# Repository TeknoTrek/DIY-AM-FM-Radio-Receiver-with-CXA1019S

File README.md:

# DIY AM/FM Radio Receiver with Sony CXA1019S - KiCad Project  

🚀 **Build your own high-quality AM/FM radio receiver** using the **Sony CXA1019S IC**! This repository contains the complete **KiCad PCB design**, schematic, and BOM for a powerful DIY radio project.  

🎥 **Watch the Full Build Tutorial on YouTube:**  
[👉 Click here to watch the video](https://youtu.be/TuUUNz7IGRk)

## 📌 Features  
✔ **Dual-band reception** (AM + FM)  
✔ **Low-noise Sony CXA1019S IC** for clear audio  
✔ **KiCad 6/7 compatible** design files  
✔ **Step-by-step YouTube tutorial** ([Watch Here](https://youtu.be/TuUUNz7IGRk))  

## 📁 Files Included
- 📐 Circuit schematic file (KiCad)
- 🧩 PCB layout
- 📸 Images and renders of the circuit
- 📄 Bill of materials (components list)

## 📦 Requirements
To complete this project, you’ll need:
- CXA1019S IC
- Basic electronic components (resistors, capacitors, etc.)
- Soldering iron & tools
- Access to KiCad (Free PCB design software)

## 🔧 How to Use  
1. **Download KiCad** (if you don’t have it): [kicad.org](https://www.kicad.org)  
2. Clone this repo or download the `.zip` file.  
3. Open the `.kicad_pro` file in KiCad to modify the design.  
4. Check the **BOM** for required components.  
5. Watch the **[assembly tutorial on YouTube](https://youtu.be/TuUUNz7IGRk)** for step-by-step guidance.  

## 📺 Watch the Full Tutorial  
  
Learn how to assemble and troubleshoot the circuit in the **[full video guide](https://youtu.be/TuUUNz7IGRk)** on the **TeknoTrek** channel!  

## 📸 Project Images

## 💬 Questions or Feedback?
Feel free to open an issue or leave a comment on the [YouTube video](https://youtu.be/TuUUNz7IGRk). I’d love to hear your thoughts and help if you get stuck!

## 📡 Tags & Keywords (for SEO)
`AM radio receiver`, `FM radio project`, `Sony CXA1019S`, `build a radio`, `DIY electronics`, `PCB design`, `KiCad project`, `radio circuit`, `home radio`, `electronics tutorial`, `radio IC`, `radio PCB`, `TeknoTrek`, `radio receiver project`, `electronics for beginners`

## ❓ FAQ  
**Q: Can I modify the PCB for better performance?**  
A: Yes! The KiCad files are fully editable. Optimize traces or add filters as needed.  

**Q: Where can I buy the CXA1019S IC?**  
A: Check AliExpress, eBay, or local electronics stores.  

## 🌟 Support the Project  
- **Give a ⭐ on GitHub** if you find this useful!  
- **Subscribe to [TeknoTrek on YouTube](https://www.youtube.com/@TeknoTrek)** for more DIY electronics projects.  
- **Share your build** in the Discussions section!  

📢 **Disclaimer**: This is an open-source project. Use at your own risk.  

#electronics #diy #radio #cxA1019s #pcbdesign #kicad #amfmradio #engineering #teknopatik

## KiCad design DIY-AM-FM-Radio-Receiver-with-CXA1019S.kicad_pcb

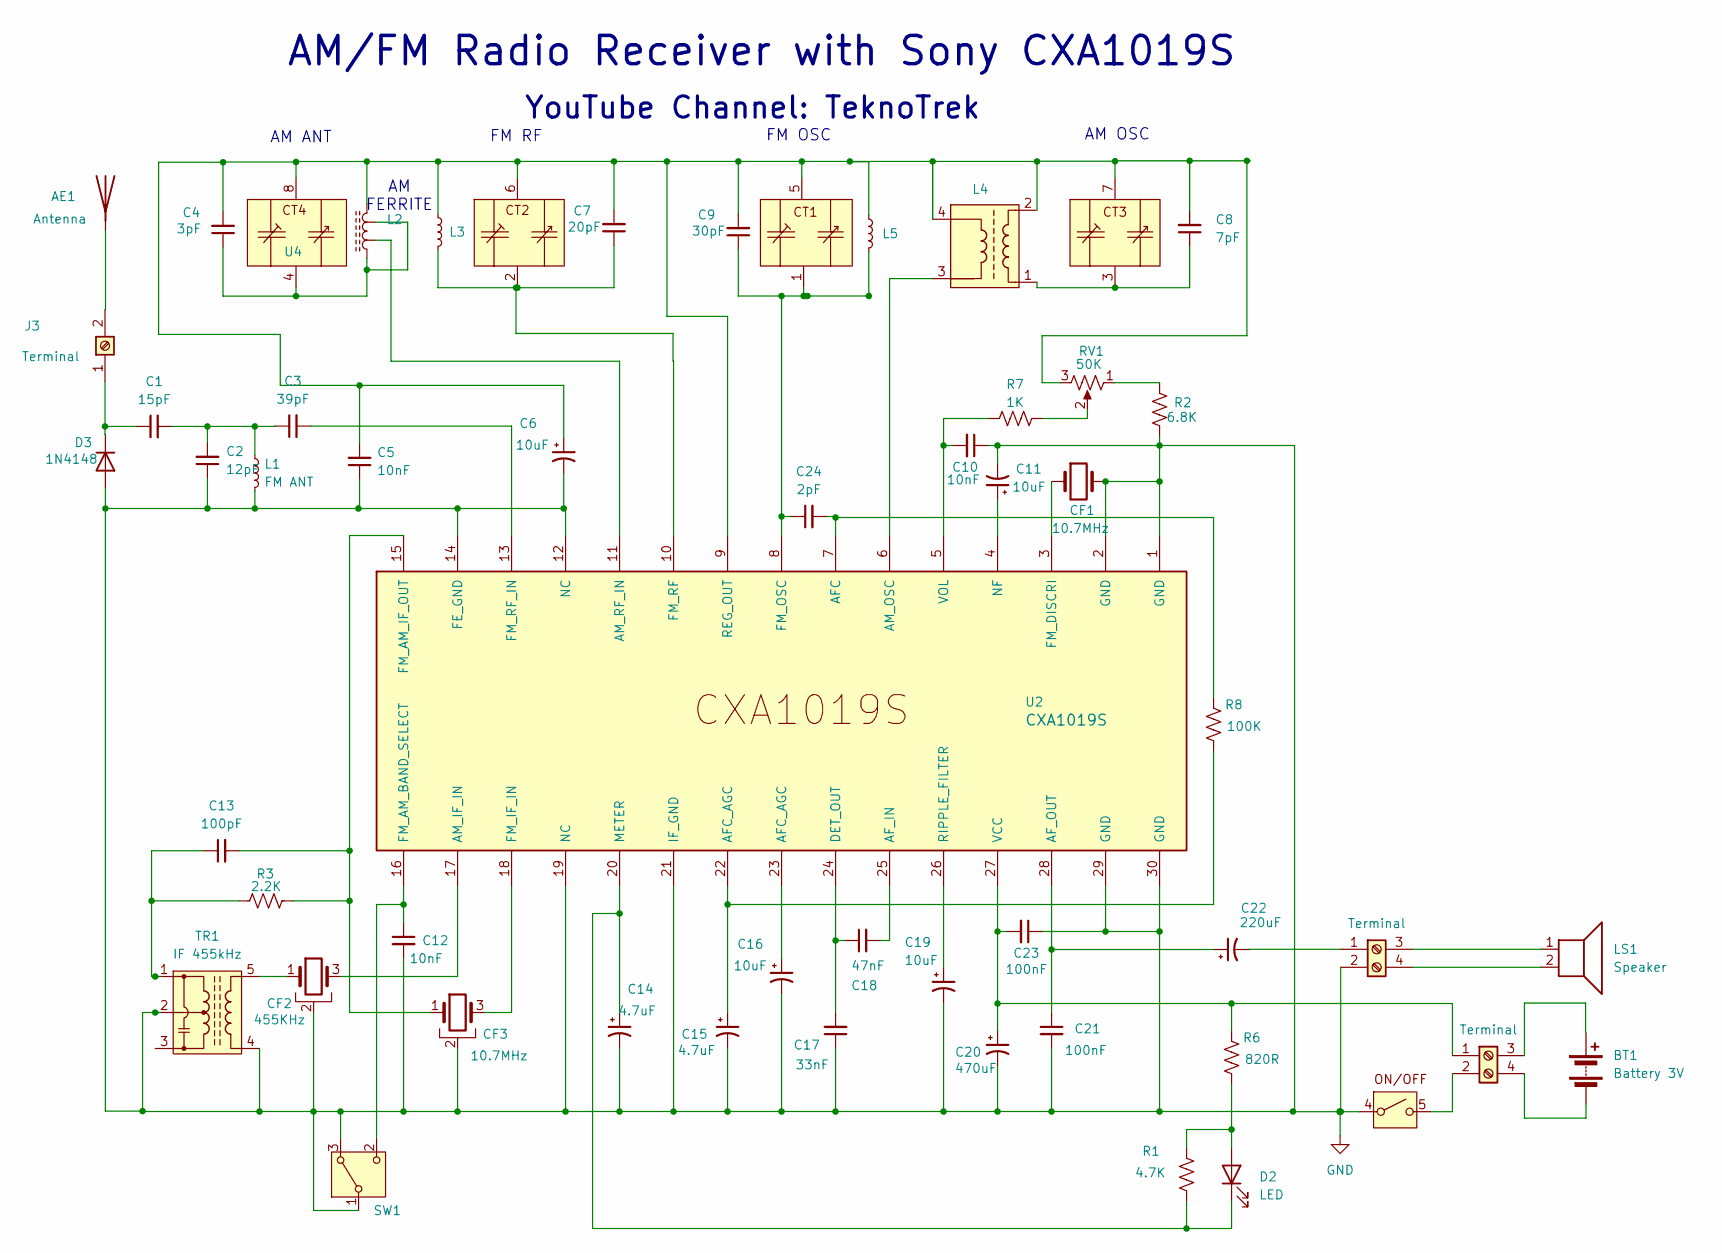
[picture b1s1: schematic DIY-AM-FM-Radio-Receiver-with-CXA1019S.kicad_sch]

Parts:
AE1: Antenna
BT1: Battery 3V
C1: 15pF; Standart_pF_Capasitor
C2: 12pF; Standart_pF_Capasitor
C3: 39pF; 39pF_Capasitor
C4: 3pF; Standart_pF_Capasitor
C5, C10, C12: 10nF; 10nF_Capasitor
C6, C11, C16, C19: 10uF; 10uF_Capasitor
C7: 20pF; Standart_pF_Capasitor
C8: 7pF; Standart_pF_Capasitor
C9: 30pF; Standart_pF_Capasitor
C13: 100pF; Standart_pF_Capasitor
C14, C15: 4.7uF; 4_7uF_Capasitor
C17: 33nF; 33nF_Capasitor
C18: 47nF; 47nF_Capasitor
C20: 470uF; 470uF_Capasitor
C21, C23: 100nF; 100nF_Capasitor
C22: 220uF; 220uF_Capasitor
C24: 2pF; 2_2pF_Capasitor
CF1: 10.7MHz; Resonator-2Pin_W6.0mm_H3.0mm
CF2: 455KHz; Resonator-3Pin_W7.0mm_H2.5mm
CF3: 10.7MHz; Resonator-3Pin_W6.0mm_H3.0mm
D2: LED; LED_D3.0mm
D3: 1N4148; D_DO-35_SOD27_P7.62mm_Horizontal
J1, J2: Terminal; PinHeader_1x02_P2.54mm_Vertical
J3: Terminal; PinHeader_1x01_P2.54mm_Vertical
L1: FM ANT; L1
L2: L_Ferrite; Am_Ferit_Ant
L3: L3
L4: AM OSC; L4_AM_OSC
L5: L5
LS1: Speaker
R1: 4.7K; R_Axial_DIN0207_L6.3mm_D2.5mm_P10.16mm_Horizontal
R2: 6.8K; R_Axial_DIN0207_L6.3mm_D2.5mm_P10.16mm_Horizontal
R3: 2.2K; R_Axial_DIN0207_L6.3mm_D2.5mm_P10.16mm_Horizontal
R6: 820R; R_Axial_DIN0207_L6.3mm_D2.5mm_P10.16mm_Horizontal
R7: 1K; R_Axial_DIN0207_L6.3mm_D2.5mm_P10.16mm_Horizontal
R8: 100K; R_Axial_DIN0207_L6.3mm_D2.5mm_P10.16mm_Horizontal
RV1: 50K; R_Pot_Switch_Footer
SW1: SW_Wuerth_450301014042; SW_Slide
TR1: IF 455kHz; IFT_455_Khz
U2: CXA1019S; SDIP-30_W11.43mm
U4: Varyabl

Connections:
GND: C2.1, C5.1, C6.2, C10.1, C11.2, C12.2, C14.2, C15.2, C16.2, C17.1, C19.2, C20.2, C21.2, C23.1, CF1.2, CF2.2, CF3.2, D3.2 (A), J1.2, L1.2, R2.2, RV1.4, SW1.1 (B), SW1.3 (A), TR1.2, TR1.4, U2.1 (GND), U2.2 (GND), U2.12 (NC), U2.14 (FE_GND), U2.19 (NC), U2.21 (IF_GND), U2.29 (GND), U2.30 (GND)
unnamed: AE1.1, J3.2
unnamed: BT1.1 (+), J2.3
unnamed: BT1.2 (-), J2.4
unnamed: C1.2, C2.2, C3.1, L1.1
unnamed: C4.1, L2.1, L2.3, U4.4
unnamed: C8.1, L4.1, U4.3
unnamed: C13.1, R3.1, TR1.1
unnamed: C15.1, R8.2, U2.22 (AFC_AGC)
unnamed: C16.1, U2.23 (AFC_AGC)
unnamed: C22.2, J1.1
unnamed: CF2.1, TR1.5
unnamed: D2.2 (A), R1.1, R6.2
unnamed: C14.1, D2.1 (K), R1.2, U2.20 (METER)
unnamed: C1.1, D3.1 (K), J3.1
unnamed: J2.2, RV1.5
unnamed: J1.3, LS1.1
unnamed: J1.4, LS1.2
unnamed: R2.1, RV1.1
unnamed: R7.2, RV1.2
unnamed: C12.1, SW1.2 (C), U2.16 (FM_AM_BAND_SELECT)
unnamed: C24.2, R8.1, U2.7 (AFC)
unnamed: C18.2, U2.25 (AF_IN)
unnamed: C21.1, C22.1, U2.28 (AF_OUT)
unnamed: CF2.3, U2.17 (AM_IF_IN)
unnamed: L4.3, U2.6 (AM_OSC)
unnamed: L2.2, U2.11 (AM_RF_IN)
unnamed: C17.2, C18.1, U2.24 (DET_OUT)
unnamed: C13.2, CF3.1, R3.2, U2.15 (FM_AM_IF_OUT)
unnamed: CF1.1, U2.3 (FM_DISCRI)
unnamed: CF3.3, U2.18 (FM_IF_IN)
unnamed: C9.1, C24.1, L5.2, U2.8 (FM_OSC), U4.1
unnamed: C7.1, L3.2, U2.10 (FM_RF), U4.2
unnamed: C3.2, U2.13 (FM_RF_IN)
unnamed: C11.1, U2.4 (NF)
unnamed: C4.2, C5.2, C6.1, C7.2, C8.2, C9.2, L2.4, L3.1, L4.2, L4.4, L5.1, RV1.3, U2.9 (REG_OUT), U4.5, U4.6, U4.7, U4.8
unnamed: C19.1, U2.26 (RIPPLE_FILTER)
unnamed: C20.1, C23.2, J2.1, R6.1, U2.27 (VCC)
unnamed: C10.2, R7.1, U2.5 (VOL)

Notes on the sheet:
AM FERRITE
FM RF
YouTube Channel: TeknoTrek
AM/FM Radio Receiver with Sony CXA1019S
AM OSC
FM OSC
AM ANT

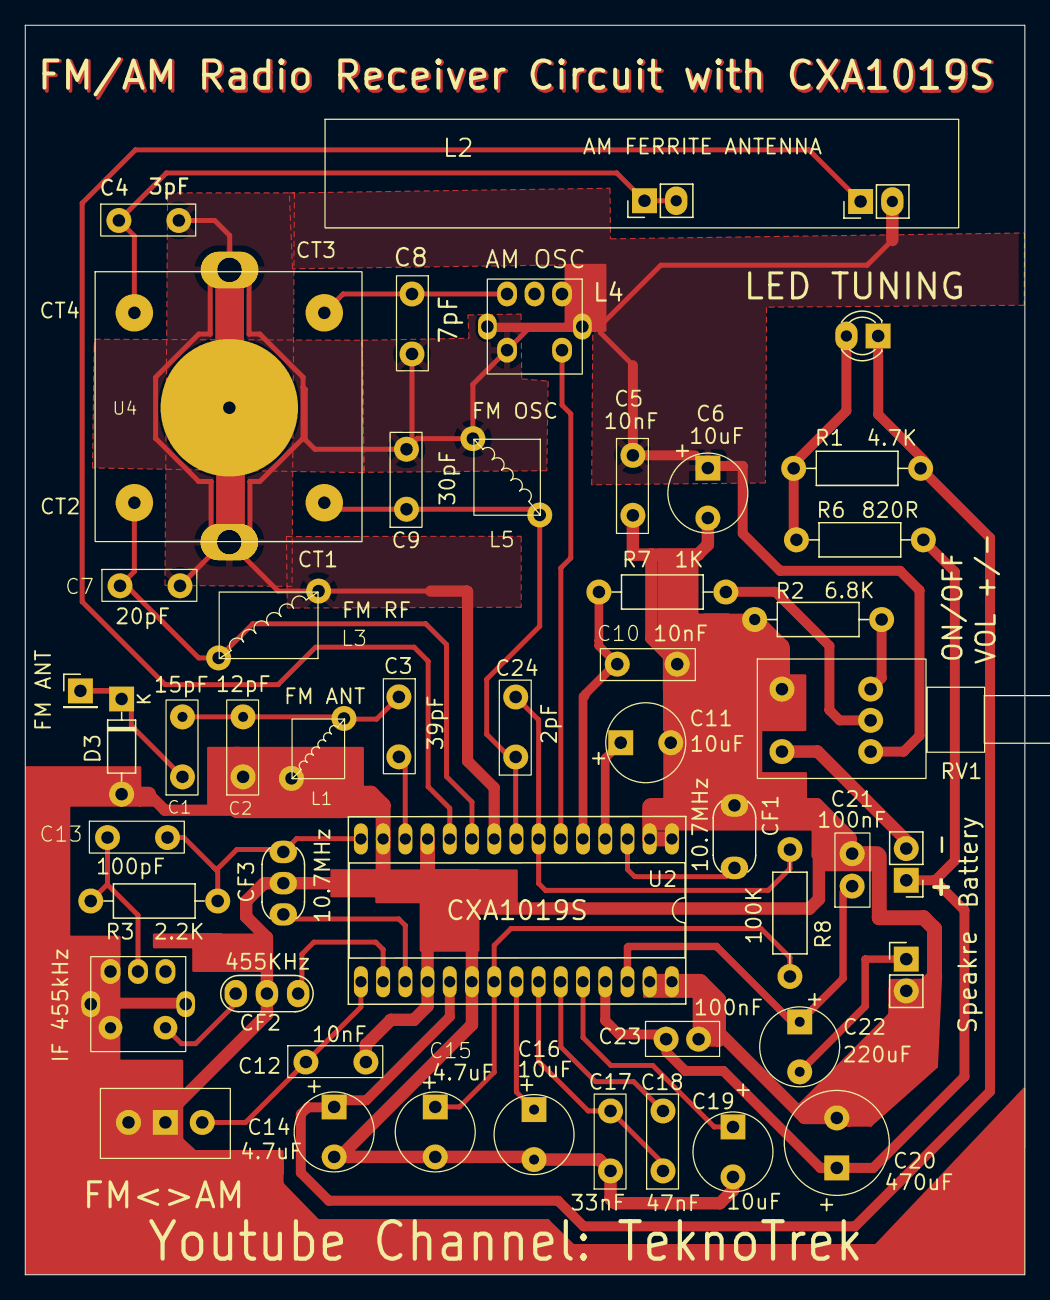
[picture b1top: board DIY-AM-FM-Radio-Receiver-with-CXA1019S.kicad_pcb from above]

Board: 2 copper layers, 80.0 x 100.0 mm, 48 parts (0 on the bottom side), 34 nets.

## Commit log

2025-04-15 Readme Update
2025-06-07 Fix urls
2025-06-07 Remove the useless spaces
2025-06-07 Restore the existing space
